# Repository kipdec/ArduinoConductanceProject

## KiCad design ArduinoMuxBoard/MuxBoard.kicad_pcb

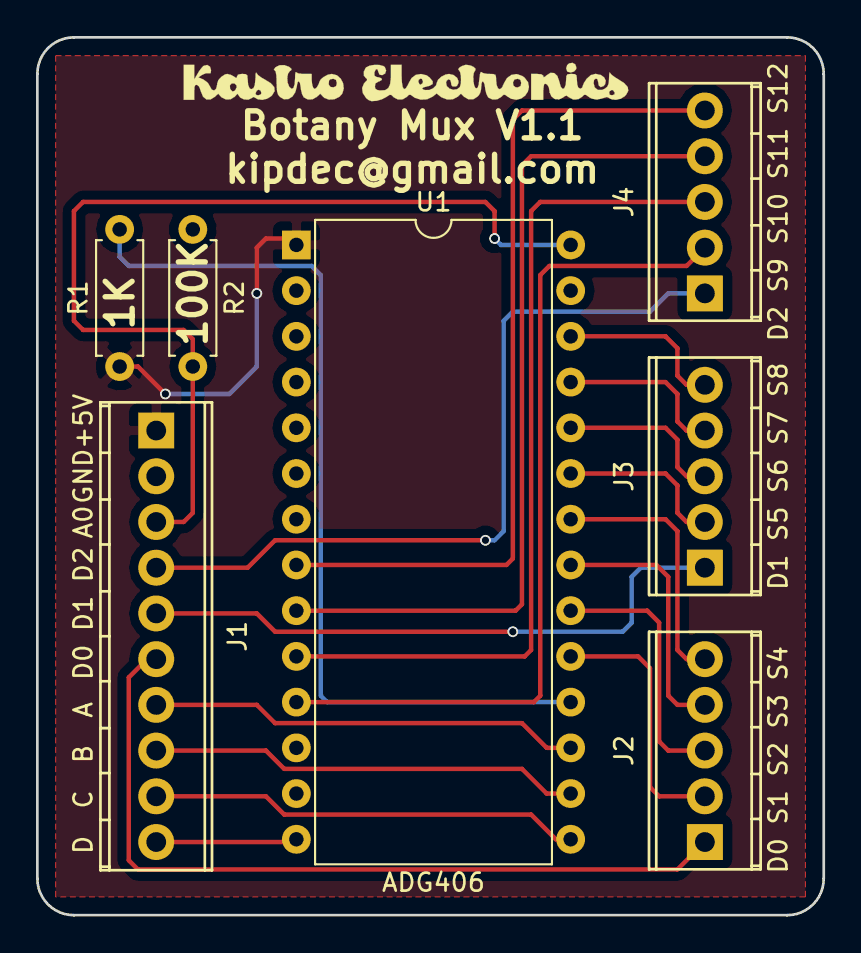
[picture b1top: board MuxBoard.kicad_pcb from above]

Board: 2 copper layers, 43.7 x 48.8 mm, 7 parts (0 on the bottom side), 23 nets.

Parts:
J1: Screw_Terminal_1x10; TerminalBlock_Pheonix_MPT-2.54mm_10pol
J2, J3, J4: Screw_Terminal_1x05; TerminalBlock_Pheonix_MPT-2.54mm_5pol
R1, R2: R; R_Axial_DIN0207_L6.3mm_D2.5mm_P7.62mm_Horizontal
U1: ADG406; DIP-28_W15.24mm

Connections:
unnamed: J1.1, R1.1, U1.1
unnamed: J1.2, R2.1, U1.12
unnamed: J1.3, R2.2, U1.28
unnamed: J1.4, J4.1
unnamed: J1.5, J3.1
unnamed: J1.6, J2.1
unnamed: J1.7, U1.17
unnamed: J1.8, U1.16
unnamed: J1.9, U1.15
unnamed: J1.10, U1.14
unnamed: J2.2, U1.19
unnamed: J2.3, U1.20
unnamed: J2.4, U1.21
unnamed: J2.5, U1.22
unnamed: J3.2, U1.23
unnamed: J3.3, U1.24
unnamed: J3.4, U1.25
unnamed: J3.5, U1.26
unnamed: J4.2, U1.11
unnamed: J4.3, U1.10
unnamed: J4.4, U1.9
unnamed: J4.5, U1.8
unnamed: R1.2, U1.18

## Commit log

2017-07-17 This is a sloppy testing file for logging purposes
2017-07-17 Arduino CSV to SD - Date and Time
2017-07-17 This is to make the data easier to analyze
2017-07-18 Made things a little less sloppy and added pcb and schematics
2017-07-18 Added simplified version that only outputs the raw value from the Arduino
2017-07-18 Figuring out Arduino to Resistance
    Whooo lots of stuff to do with figuring out the relationship between
    voltage and resistance for the Arduino
2017-07-18 Error calculation
    Bad did error calculation
2017-07-19 Notes for the functions we used
    These functions were gleaned from Tim’s research and our experimental
    data
2017-07-19 Mux interpreter
    This code will serve as the basis for our master code. As of yet
    untested.
2017-07-19 Std Deviation added
    Bal added standard deviation to this data set
